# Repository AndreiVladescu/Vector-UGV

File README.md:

# V.E.C.T.O.R.

An 18-DOF hexapod research platform: a smart controller per leg on CAN, a Raspberry Pi CM5 carrier, camera and SDR payload, ELRS / Wi-Fi / 4G links. Built for the [PCBWay 9th Project Design Contest](https://www.pcbway.com/activity/9th-project-design-contest.html).

- `docs/`: spec, connector pinouts, power budget, servo names and calibration
- `hardware/`: one KiCad project per board, shared library in `lib/`
- `mechanical/`: Fusion 360 exports (STEP, STL), harness drawings
- `firmware/`: STM32C092 code for the leg and power nodes, CAN bootloader
- `software/`: CM5 / Pi 5 side: ROS 2 workspace, tools, Docker
- `protocol/vector.dbc`: CAN message definitions, used by firmware and host
- `test-tools/`: bench sketches, e.g. `servo_test` (Arduino Uno, set a servo angle over serial and read the pot)

Start with `docs/spec.md`.

## Try it without hardware

Everything below runs on a PC with Ubuntu 24.04 or Linux Mint 22 and ROS 2 Jazzy (install commands in [`software/README.md`](software/README.md#desktop-setup-mint-223--ubuntu-2404)). The leg nodes run their real firmware logic against simulated servos on a virtual CAN bus.

```sh
cd software/ros2_ws
source /opt/ros/jazzy/setup.zsh                 # or setup.bash
colcon build --symlink-install && source install/setup.zsh

# virtual CAN bus (again after every reboot)
sudo modprobe vcan
sudo ip link add dev vcan0 type vcan && sudo ip link set up vcan0

ros2 run vector_hw sim_legs vcan0 --calibrated --limits -45.8,45.8,-80.2,80.2,-149,17  # terminal 1: six legs
ros2 launch vector_bringup robot.launch.py hardware:=can can_interface:=vcan0   # terminal 2: robot + rviz
ros2 run teleop_twist_keyboard teleop_twist_keyboard                           # terminal 3: drive (i, j, l, J, L, t, b, k)
candump vcan0 | cantools decode ../../protocol/vector.dbc                      # optional: watch the bus
```

Each new terminal needs the two `source` lines. Stop `sim_legs` while the robot runs and the hardware drops out after 100 ms, the same as it would with a dead leg. Without `--calibrated` the legs start like fresh boards; `leg_config.py` calibrates them (see `software/README.md`).

Without CAN: `robot.launch.py` alone (mock joints), or `sim_gazebo.launch.py world:=rough level:=true` for physics.

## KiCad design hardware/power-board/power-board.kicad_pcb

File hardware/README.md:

# Hardware

One KiCad project per board: `side-board/`, `power-board/`, `carrier-cm5/`. The lib tables in each point to the shared library in `lib/`, so custom symbols and footprints go there.

- Connector pinouts come from `docs/interfaces.md`. Use the same footprint and pin order on both ends of a cable.
- Side board: draw the leg cell as one hierarchical sheet, use it three times, and copy the layout with KiCad's multichannel tools.
- Tag each fabbed revision (`side-board-revA`) and put the revision and git hash on the silkscreen. Gerbers, BOM and pick-and-place go in `<board>/production/<rev>/`.
- Hand assembly: 0402 minimum, one side where possible, test points and 0 Ω links on every rail.

`BOM_LCSC.csv` is a second way to buy the main parts for one robot: LCSC part numbers, quantities, prices and stock checked on 2026-10-08, and where each part is cheaper (LCSC, Mouser or TME). It loads straight into LCSC's BOM tool. Passives aren't in it yet.

## Power rails

Currents and loads are in `docs/power-budget.md`. No 5 V on the side boards: the CAN transceivers are 3.3 V parts (TI TCAN332DR).

```
PACK 4S3P 18650 (12.0–16.8 V)
│
└─ POWER BOARD ── BQ76952 high-side FETs ── VBAT
   │                                  (charging: BQ25798, fed by GX-12 12–24 V or USB-C PD 20 V)
   │
   ├─ LM5069 (hot-swap + e-stop) ── VBAT_L ──► SIDE BOARD L
   │                                  ├─ TPS56A37 ── 6V0_LEG1 ── 3× MG996R (+ pots)
   │                                  ├─ TPS56A37 ── 6V0_LEG2 ── 3× MG996R (+ pots)
   │                                  ├─ TPS56A37 ── 6V0_LEG3 ── 3× MG996R (+ pots)
   │                                  └─ low-Iq buck ── 3V3_LEG ── 3× STM32C092, 3× CAN xcvr,
   │                                                              3× VL53L1X, 3× INA181
   │
   ├─ LM5069 (hot-swap + e-stop) ── VBAT_R ──► SIDE BOARD R   (same as L)
   │
   ├─ 5 V / 6 A buck ── 5V_SYS ──► CARRIER
   │                                  ├─ CM5 ── 3V3 / 1V8 (CM5's own outputs)
   │                                  ├─ 2× USB-A (current-limit switches)
   │                                  ├─ SDR (AD9363), fan
   │                                  └─ 3V3_M2 ── Hailo M.2 (optional)
   │
   ├─ VBAT_SYS ──► CARRIER
   │                ├─ 3.8 V buck ── 3V8_LTE ── EC25-EUX
   │                └─ small 5 V buck ── gimbal (2× SG90)
   │
   └─ 3V3_PWR (TBD) ── STM32C092 on the power board, BQ76952 comms
```

3.3 V is made locally on each side board, not sent over the CAN harness: the STM32C0 ADC uses VDD as its reference, so a remote 3.3 V would put servo current noise on the pot and current readings, and a short on one side would take down the other.

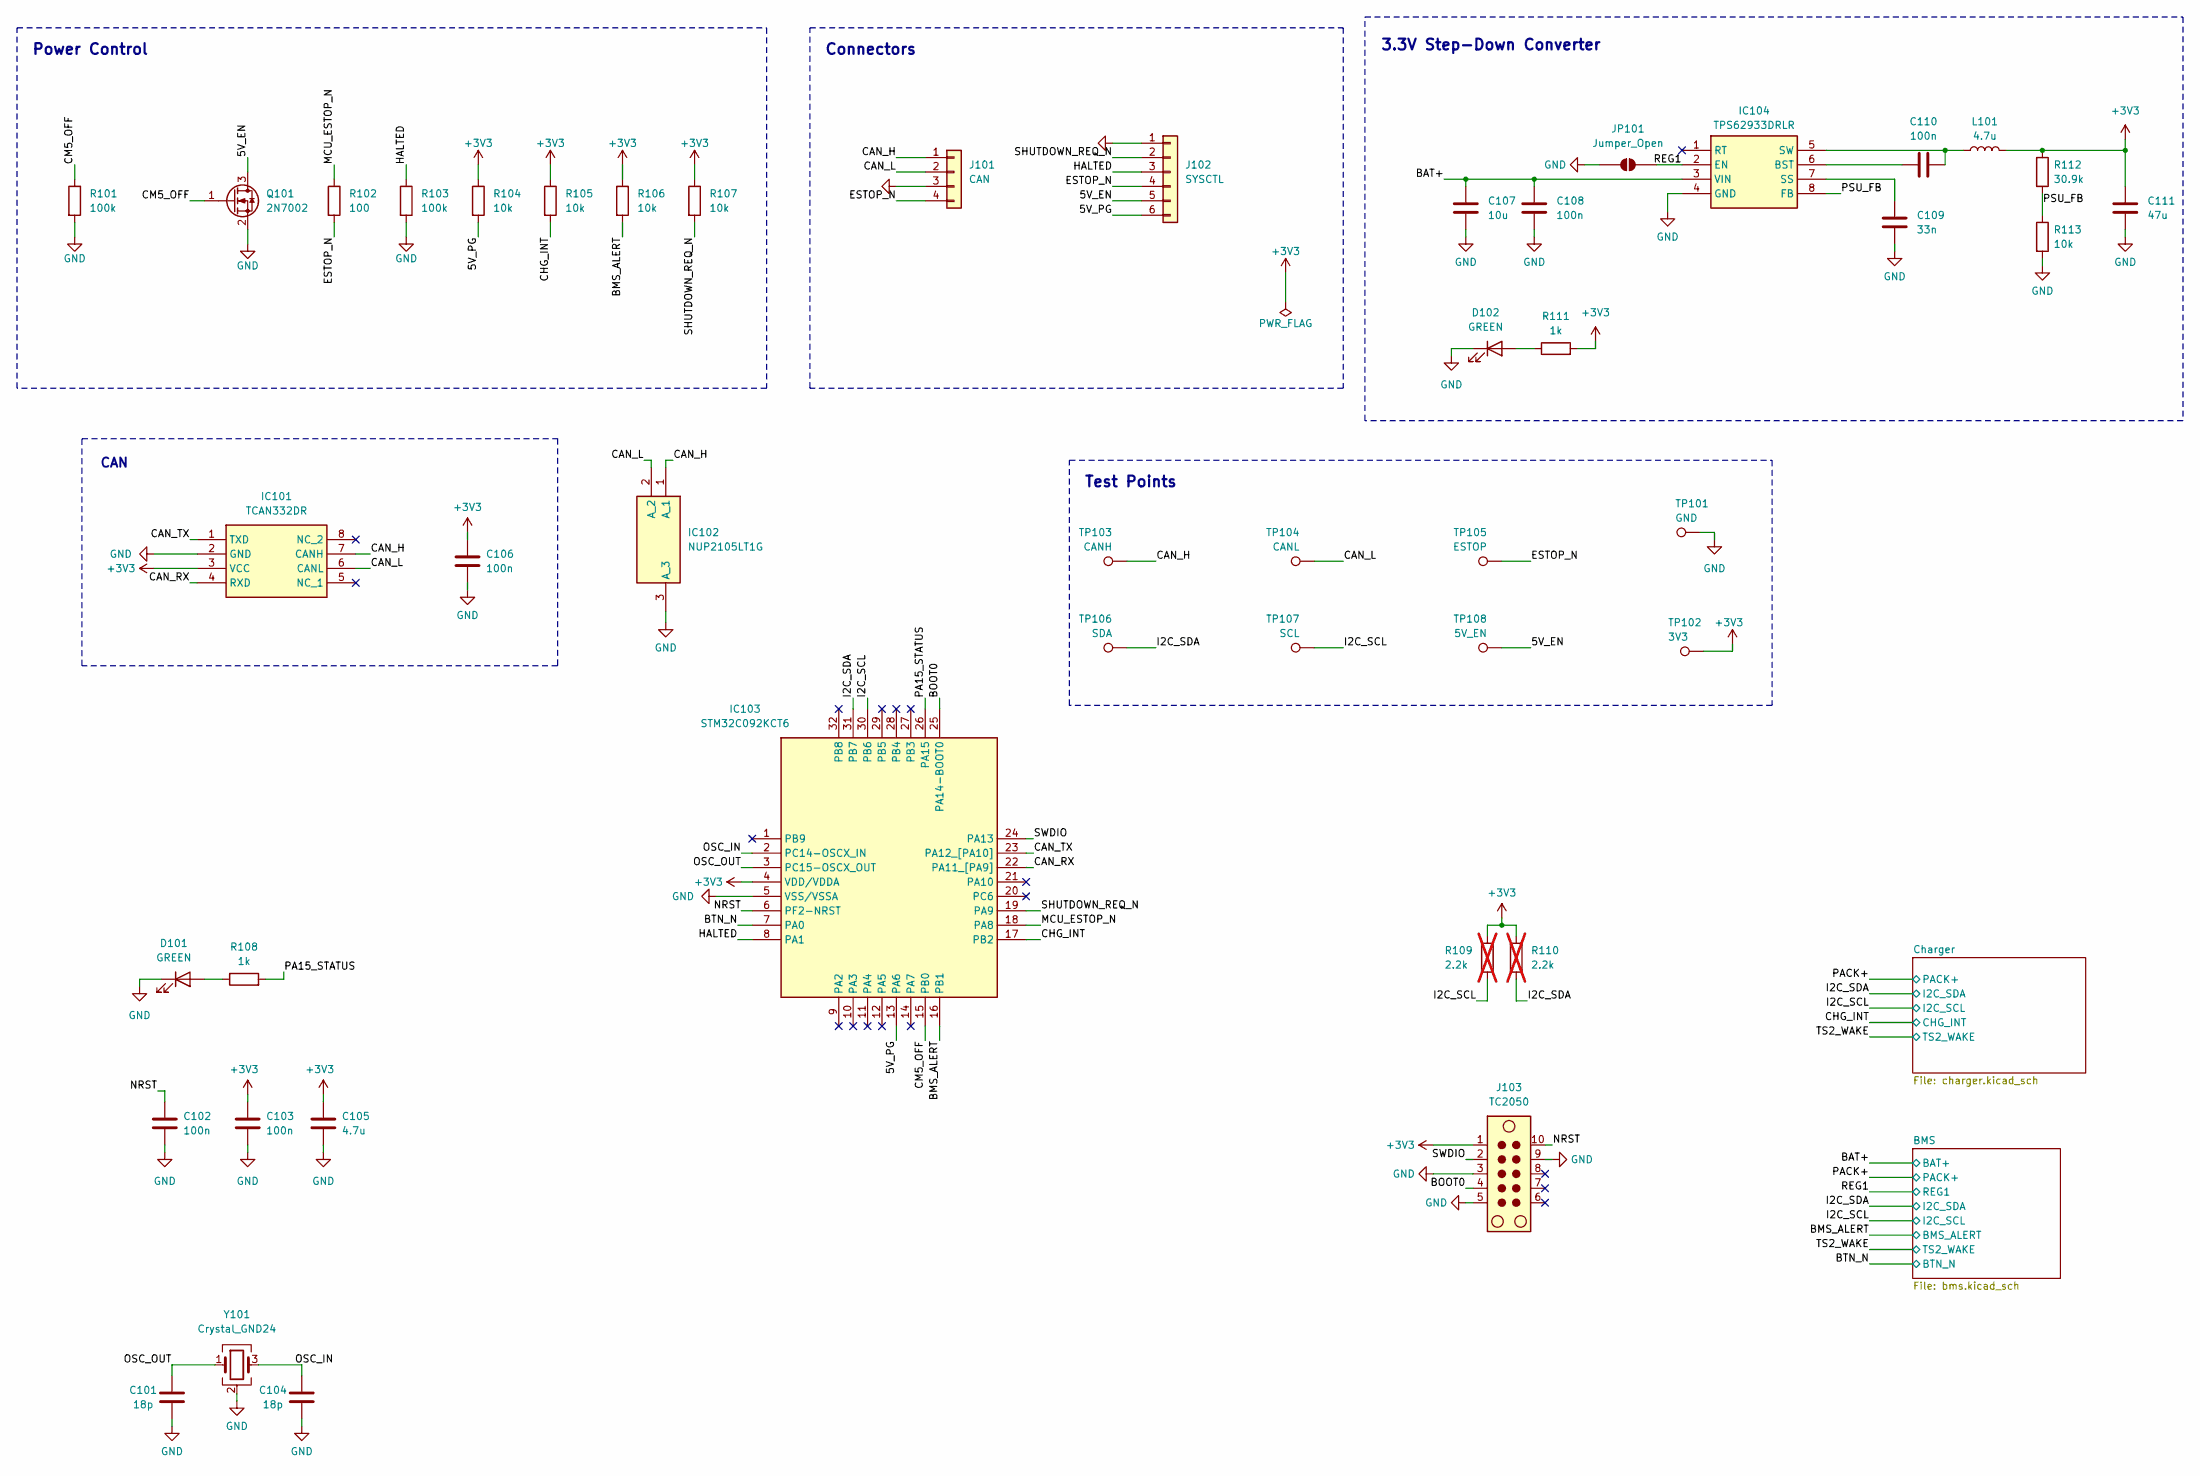
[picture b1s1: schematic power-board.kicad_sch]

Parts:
C101, C104: 18p; C_0805_2012Metric
C102, C103, C106, C108, C110: 100n; C_0805_2012Metric
C105: 4.7u; C_0805_2012Metric
C107: 10u; C_0805_2012Metric
C109: 33n; C_0805_2012Metric
C111: 47u; C_0805_2012Metric
D101, D102: GREEN; LED_0805_2012Metric
IC101: TCAN332DR; SOIC127P600X175-8N; Mouser Part Number 595-TCAN332DR
IC102: NUP2105LT1G; SOT96P237X111-3N; Mouser Part Number 863-NUP2105LT1G
IC103: STM32C092KCT6; QFP80P900X900X160-32N; Mouser Part Number 511-STM32C092KCT6
IC104: TPS62933DRLR; SOTFL50P160X60-8N; Mouser Part Number 595-TPS62933DRLR
J101: CAN; JST_XH_S4B-XH-A-1_1x04_P2.50mm_Horizontal
J102: SYSCTL; JST_XH_S6B-XH-A-1_1x06_P2.50mm_Horizontal
J103: TC2050; Tag-Connect_TC2050-IDC-FP_2x05_P1.27mm_Vertical
JP101: Jumper_Open; SolderJumper-2_P1.3mm_Open_Pad1.0x1.5mm
L101: 4.7u; INDPM4441X200N; Manufacturer_Part_Number SRP4020TA-4R7M
Q101: 2N7002; SOT-23
R101, R103: 100k; R_0603_1608Metric
R102: 100; R_0603_1608Metric
R104, R105, R106, R107: 10k; R_0603_1608Metric
R108, R111: 1k; R_0603_1608Metric
R109, R110: 2.2k; R_0603_1608Metric; not fitted
R112: 30.9k; R_0805_2012Metric
R113: 10k; R_0805_2012Metric
TP101: GND; TestPoint_Pad_D2.0mm
TP102: 3V3; TestPoint_Pad_D2.0mm
TP103: CANH; TestPoint_Pad_D2.0mm
TP104: CANL; TestPoint_Pad_D2.0mm
TP105: ESTOP; TestPoint_Pad_D2.0mm
TP106: SDA; TestPoint_Pad_D2.0mm
TP107: SCL; TestPoint_Pad_D2.0mm
TP108: 5V_EN; TestPoint_Pad_D2.0mm
Y101: Crystal_GND24; Crystal_SMD_2016-4Pin_2.0x1.6mm; Manufacturer_Part_Number K2B400001210

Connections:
+3V3: C103.2, C105.2, C106.2, C111.2, IC101.3 (VCC), IC103.4 (VDD/VDDA), J103.1, L101.2, R104.1, R105.1, R106.1, R107.1, R109.1, R110.2, R111.2, R112.1, TP102.1 (1_1)
/5V_EN: J102.5, Q101.3 (D), TP108.1 (1_1)
/5V_PG: IC103.13 (PA6), J102.6, R104.2
/BAT+: C107.2, C108.2, IC104.3 (VIN); also elsewhere on the board
/BMS_ALERT: IC103.16 (PB1), R106.2; also elsewhere on the board
/BOOT0: IC103.25 (PA14-BOOT0), J103.4
/BTN_N: IC103.7 (PA0); also elsewhere on the board
/CAN_H: IC101.7 (CANH), IC102.1 (A_1), J101.1, TP103.1 (1_1)
/CAN_L: IC101.6 (CANL), IC102.2 (A_2), J101.2, TP104.1 (1_1)
/CAN_RX: IC101.4 (RXD), IC103.22 (PA11_[PA9])
/CAN_TX: IC101.1 (TXD), IC103.23 (PA12_[PA10])
/CHG_INT: IC103.17 (PB2), R105.2; also elsewhere on the board
/CM5_OFF: IC103.15 (PB0), Q101.1 (G), R101.1
/ESTOP_N: J101.4, J102.4, R102.2, TP105.1 (1_1)
/HALTED: IC103.8 (PA1), J102.3, R103.1
/I2C_SCL: IC103.30 (PB6), R109.2, TP107.1 (1_1); also elsewhere on the board
/I2C_SDA: IC103.31 (PB7), R110.1, TP106.1 (1_1); also elsewhere on the board
/MCU_ESTOP_N: IC103.18 (PA8), R102.1
/NRST: C102.2, IC103.6 (PF2-NRST), J103.10
/OSC_IN: C104.2, IC103.2 (PC14-OSCX_IN), Y101.3
/OSC_OUT: C101.2, IC103.3 (PC15-OSCX_OUT), Y101.1
/PA15_STATUS: IC103.26 (PA15), R108.2
/PSU_FB: IC104.8 (FB), R112.2, R113.1
/REG1: IC104.2 (EN), JP101.2 (B); also elsewhere on the board
/SHUTDOWN_REQ_N: IC103.19 (PA9), J102.2, R107.2
/SWDIO: IC103.24 (PA13), J103.2
GND: C101.1, C102.1, C103.1, C104.1, C105.1, C106.1, C107.1, C108.1, C109.1, C111.1, D101.1 (K), D102.1 (K), IC101.2 (GND), IC102.3 (A_3), IC103.5 (VSS/VSSA), IC104.4 (GND), J101.3, J102.1, J103.3, J103.5, J103.9, JP101.1 (A), Q101.2 (S), R101.2, R103.2, R113.2, TP101.1 (1_1), Y101.2 (G), Y101.4 (G); also elsewhere on the board
unnamed: D101.2 (A), R108.1
unnamed: D102.2 (A), R111.1
unnamed: C110.1, IC104.6 (BST)
unnamed: C109.2, IC104.7 (SS)
unnamed: C110.2, IC104.5 (SW), L101.1

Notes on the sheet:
Test Points
Power Control
CAN
3.3V Step-Down Converter
Connectors

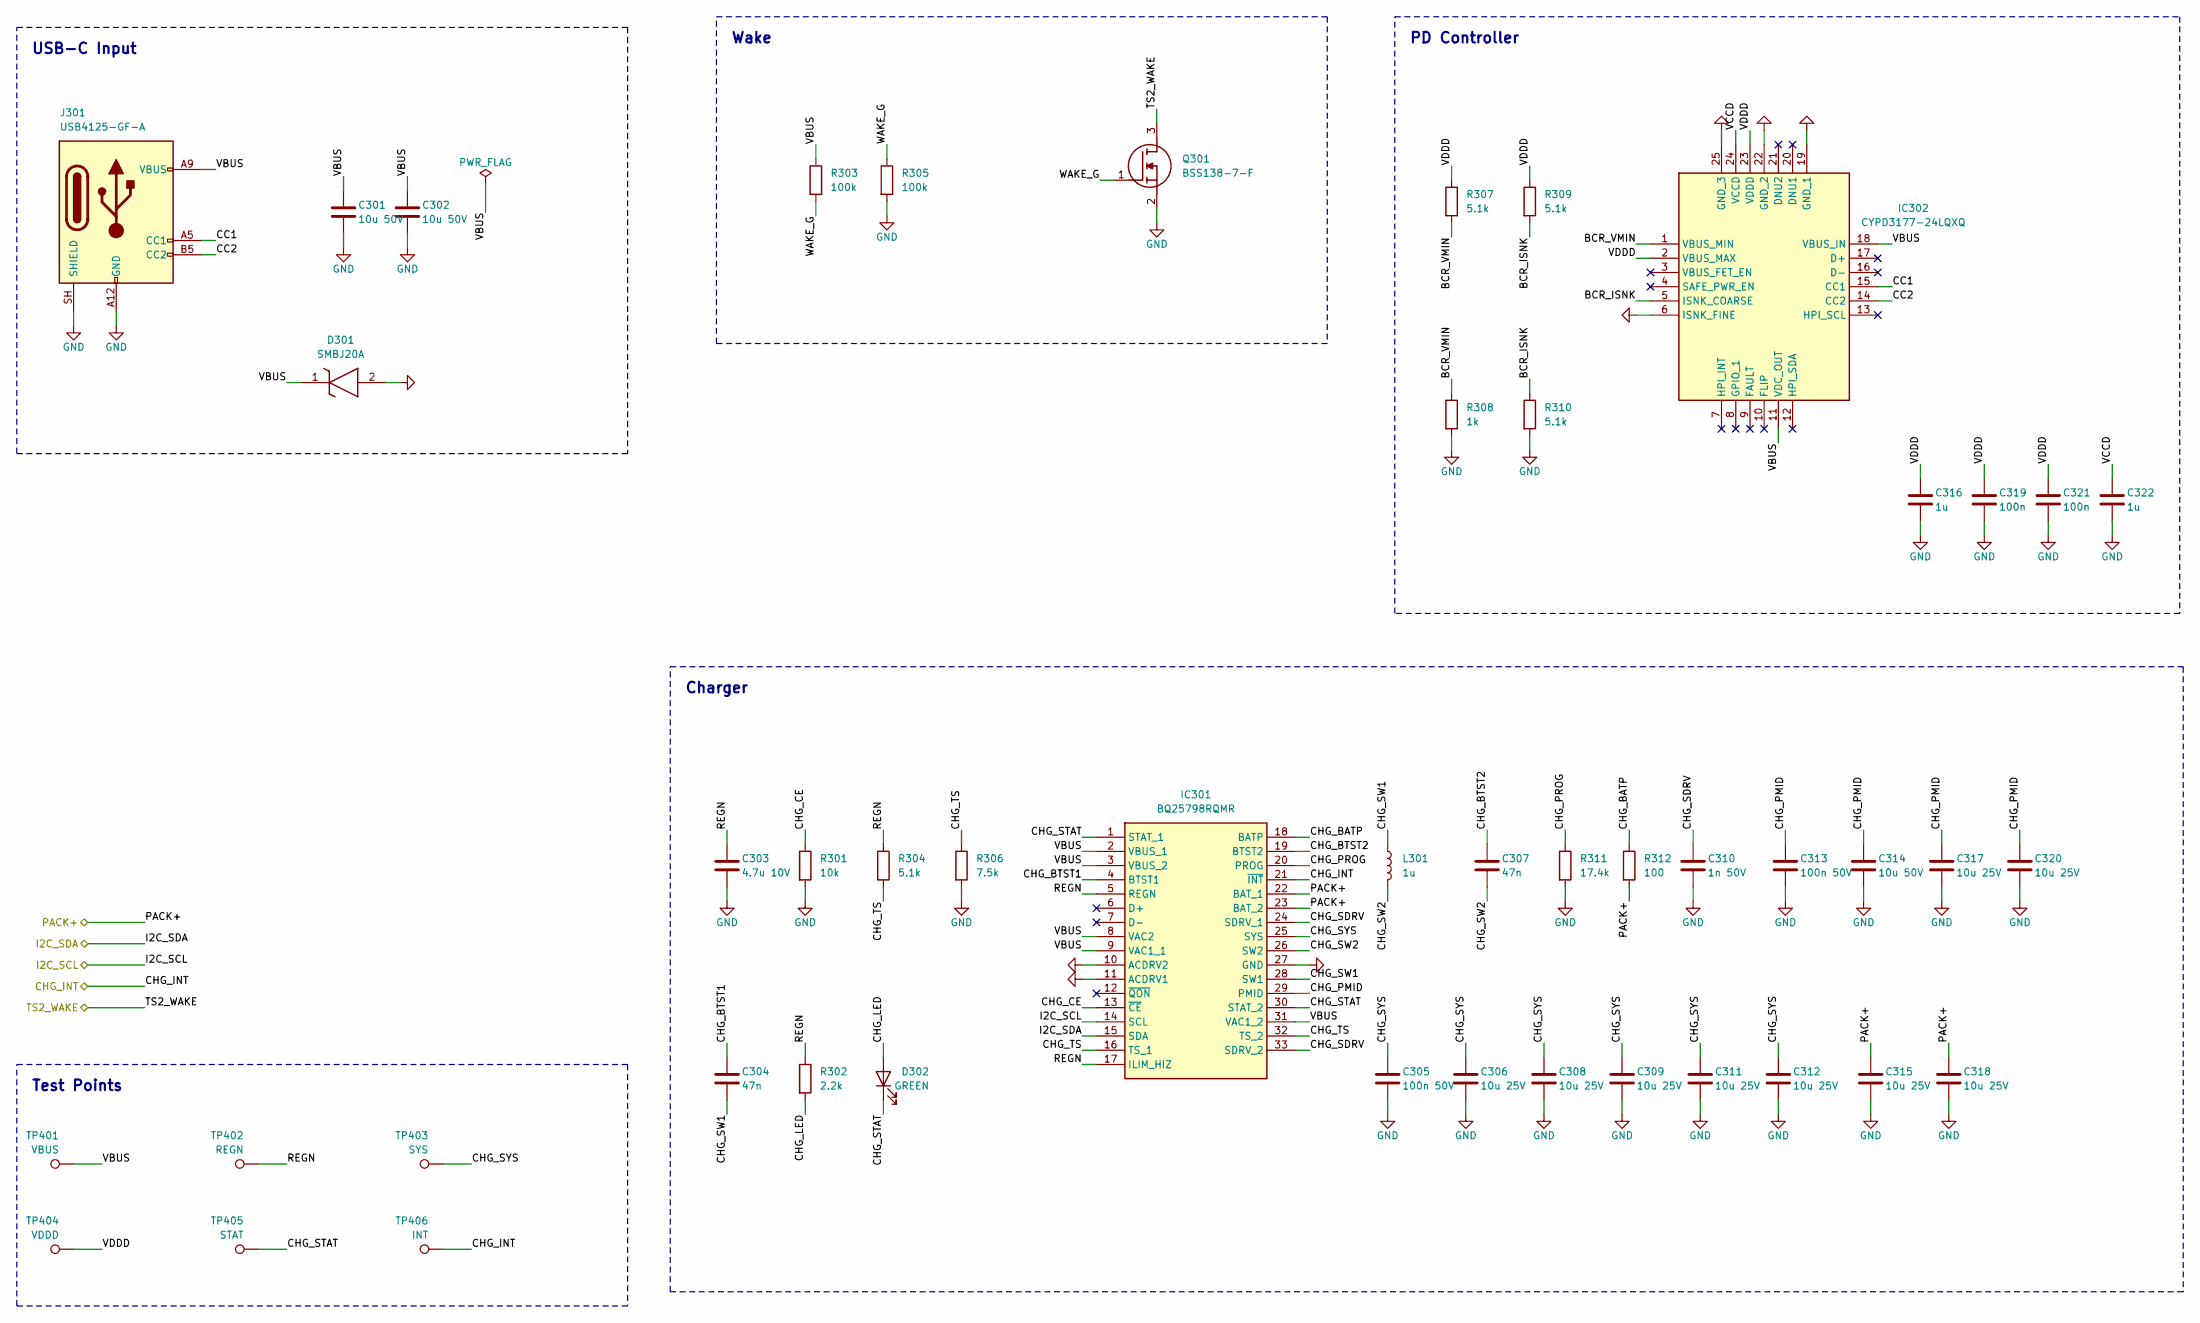
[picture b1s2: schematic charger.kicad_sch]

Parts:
C301, C302, C314: 10u 50V; C_1206_3216Metric
C303: 4.7u 10V; C_0805_2012Metric
C304, C307: 47n; C_0805_2012Metric
C305, C313: 100n 50V; C_0805_2012Metric
C306, C308, C309, C311, C312, C315, C317, C318, C320: 10u 25V; C_0805_2012Metric
C310: 1n 50V; C_0805_2012Metric
C316, C322: 1u; C_0805_2012Metric
C319, C321: 100n; C_0805_2012Metric
D301: SMBJ20A; DIOM5436X244N; Mouser Part Number 652-SMBJ20A
D302: GREEN; LED_0603_1608Metric
IC301: BQ25798RQMR; Mouser Part Number 595-BQ25798RQMR
IC302: CYPD3177-24LQXQ; QFN50P400X400X60-25N-D; Mouser Part Number 727-CYPD3177-24LQXQ
J301: USB4125-GF-A; USB_C_Receptacle_GCT_USB4125-xx-x_6P_TopMnt_Horizontal
L301: 1u; L_Coilcraft_XAL5030-XXX
Q301: BSS138-7-F; SOT96P240X115-3N; Mouser Part Number 621-BSS138-7-F
R301: 10k; R_0603_1608Metric
R302: 2.2k; R_0603_1608Metric
R303, R305: 100k; R_0603_1608Metric
R304, R307, R309, R310: 5.1k; R_0603_1608Metric
R306: 7.5k; R_0603_1608Metric
R308: 1k; R_0603_1608Metric
R311: 17.4k; R_0603_1608Metric
R312: 100; R_0603_1608Metric
TP401: VBUS; TestPoint_Pad_D2.0mm
TP402: REGN; TestPoint_Pad_D2.0mm
TP403: SYS; TestPoint_Pad_D2.0mm
TP404: VDDD; TestPoint_Pad_D2.0mm
TP405: STAT; TestPoint_Pad_D2.0mm
TP406: INT; TestPoint_Pad_D2.0mm

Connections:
/CHG_INT: IC301.21 (~INT), TP406.1 (1_1); also elsewhere on the board
/Charger/BCR_ISNK: IC302.5 (ISNK_COARSE), R309.2, R310.1
/Charger/BCR_VMIN: IC302.1 (VBUS_MIN), R307.2, R308.1
/Charger/CC1: IC302.15 (CC1), J301.A5 (CC1)
/Charger/CC2: IC302.14 (CC2), J301.B5 (CC2)
/Charger/CHG_BATP: IC301.18 (BATP), R312.1
/Charger/CHG_BTST1: C304.1, IC301.4 (BTST1)
/Charger/CHG_BTST2: C307.1, IC301.19 (BTST2)
/Charger/CHG_CE: IC301.13 (~CE), R301.1
/Charger/CHG_LED: D302.2 (A), R302.2
/Charger/CHG_PMID: C313.1, C314.1, C317.1, C320.1, IC301.29 (PMID)
/Charger/CHG_PROG: IC301.20 (PROG), R311.1
/Charger/CHG_SDRV: C310.1, IC301.24 (SDRV_1), IC301.33 (SDRV_2)
/Charger/CHG_STAT: D302.1 (K), IC301.1 (STAT_1), IC301.30 (STAT_2), TP405.1 (1_1)
/Charger/CHG_SW1: C304.2, IC301.28 (SW1), L301.1
/Charger/CHG_SW2: C307.2, IC301.26 (SW2), L301.2
/Charger/CHG_SYS: C305.1, C306.1, C308.1, C309.1, C311.1, C312.1, IC301.25 (SYS), TP403.1 (1_1)
/Charger/CHG_TS: IC301.16 (TS_1), IC301.32 (TS_2), R304.2, R306.1
/Charger/REGN: C303.1, IC301.5 (REGN), IC301.17 (ILIM_HIZ), R302.1, R304.1, TP402.1 (1_1)
/Charger/VBUS: C301.1, C302.1, D301.1 (K), IC301.2 (VBUS_1), IC301.3 (VBUS_2), IC301.8 (VAC2), IC301.9 (VAC1_1), IC301.31 (VAC1_2), IC302.11 (VDC_OUT), IC302.18 (VBUS_IN), J301.A9 (VBUS), J301.B9 (VBUS), R303.1, TP401.1 (1_1)
/Charger/VCCD: C322.1, IC302.24 (VCCD)
/Charger/VDDD: C316.1, C319.1, C321.1, IC302.2 (VBUS_MAX), IC302.23 (VDDD), R307.1, R309.1, TP404.1 (1_1)
/Charger/WAKE_G: Q301.1 (G), R303.2, R305.1
/I2C_SCL: IC301.14 (SCL); also elsewhere on the board
/I2C_SDA: IC301.15 (SDA); also elsewhere on the board
/PACK+: C315.1, C318.1, IC301.22 (BAT_1), IC301.23 (BAT_2), R312.2; also elsewhere on the board
/TS2_WAKE: Q301.3 (D); also elsewhere on the board
GND: C301.2, C302.2, C303.2, C305.2, C306.2, C308.2, C309.2, C310.2, C311.2, C312.2, C313.2, C314.2, C315.2, C316.2, C317.2, C318.2, C319.2, C320.2, C321.2, C322.2, D301.2 (A), IC301.10 (ACDRV2), IC301.11 (ACDRV1), IC301.27 (GND), IC302.6 (ISNK_FINE), IC302.19 (GND_1), IC302.22 (GND_2), IC302.25 (GND_3), J301.A12 (GND), J301.B12 (GND), J301.SH (SHIELD), Q301.2 (S), R301.2, R305.2, R306.2, R308.2, R310.2, R311.2; also elsewhere on the board

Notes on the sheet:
Wake
Test Points
PD Controller
Charger
USB-C Input

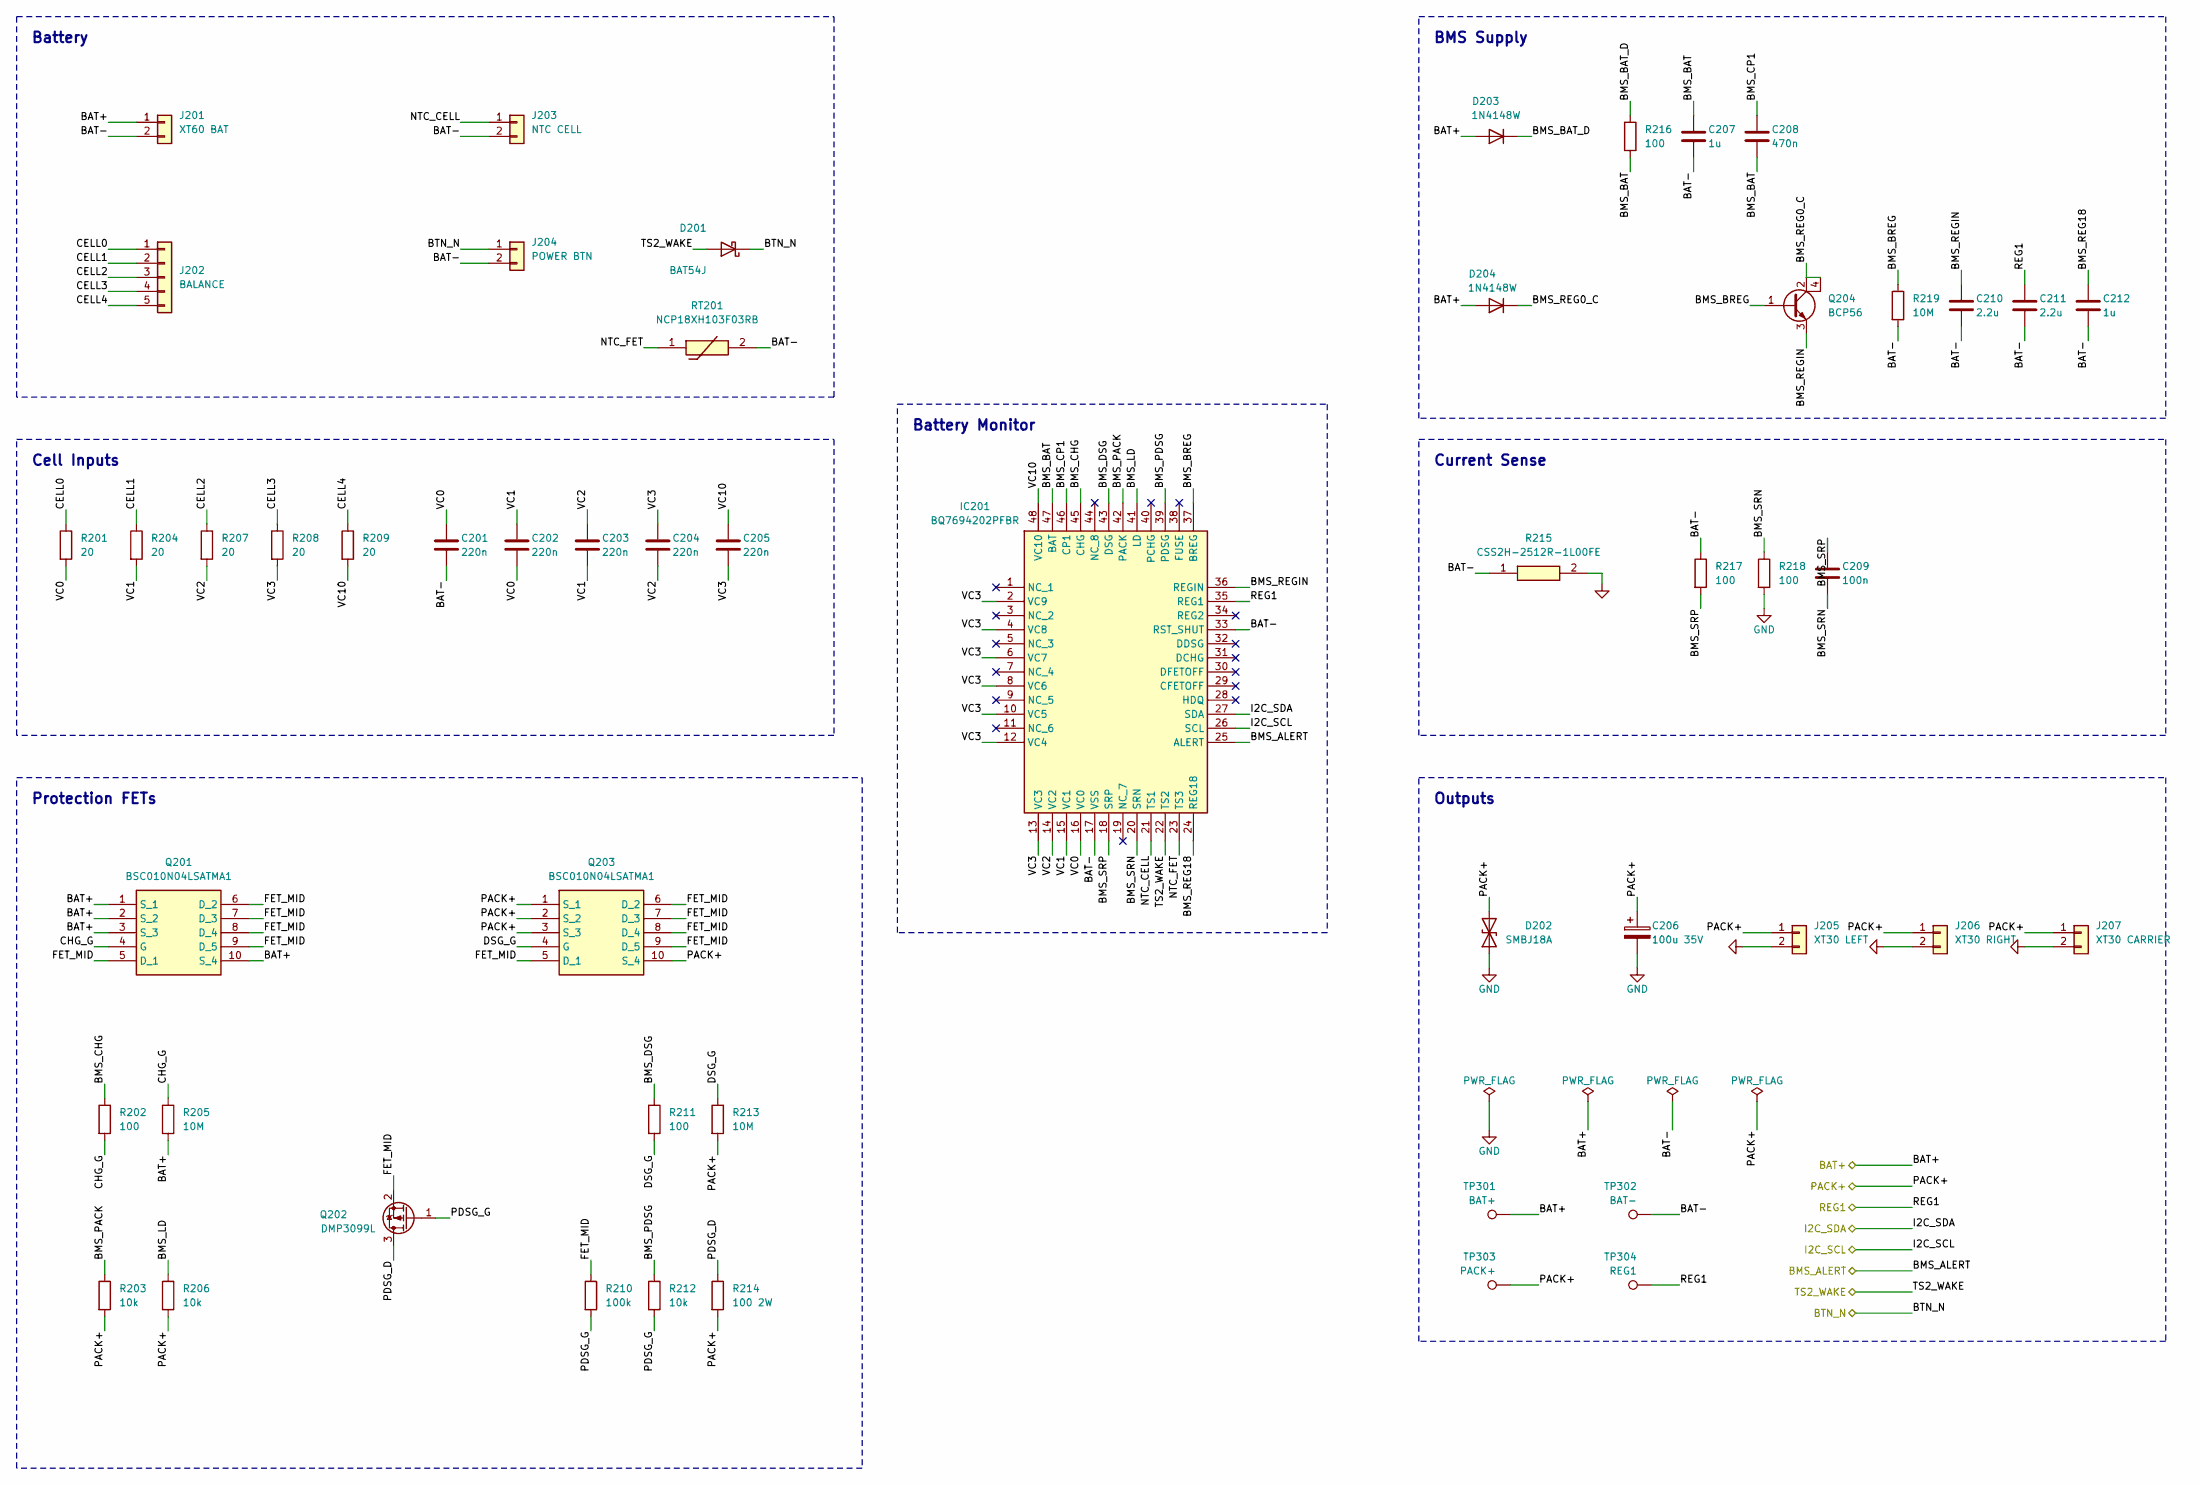
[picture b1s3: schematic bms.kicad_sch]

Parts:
C201, C202, C203, C204, C205: 220n; C_0805_2012Metric
C206: 100u 35V; CP_Elec_8x10.5
C207, C212: 1u; C_0805_2012Metric
C208: 470n; C_0805_2012Metric
C209: 100n; C_0805_2012Metric
C210, C211: 2.2u; C_0805_2012Metric
D201: BAT54J; D_SOD-323F
D202: SMBJ18A; D_SMB
D203, D204: 1N4148W; D_SOD-123
IC201: BQ7694202PFBR; QFP50P900X900X120-48N; Mouser Part Number 595-BQ7694202PFBR
J201: XT60 BAT; AMASS_XT60PW-M_1x02_P7.20mm_Horizontal
J202: BALANCE; JST_XH_B5B-XH-A_1x05_P2.50mm_Vertical
J203: NTC CELL; JST_PH_B2B-PH-K_1x02_P2.00mm_Vertical
J204: POWER BTN; JST_PH_B2B-PH-K_1x02_P2.00mm_Vertical
J205: XT30 LEFT; AMASS_XT30PW-M_1x02_P2.50mm_Horizontal
J206: XT30 RIGHT; AMASS_XT30PW-M_1x02_P2.50mm_Horizontal
J207: XT30 CARRIER; AMASS_XT30PW-M_1x02_P2.50mm_Horizontal
Q201, Q203: BSC010N04LSATMA1; Mouser Part Number 726-BSC010N04LSATMA1
Q202: DMP3099L; SOT-23
Q204: BCP56; SOT-223
R201, R204, R207, R208, R209: 20; R_0603_1608Metric
R202, R211, R216, R217, R218: 100; R_0603_1608Metric
R203, R206, R212: 10k; R_0603_1608Metric
R205, R213, R219: 10M; R_0603_1608Metric
R210: 100k; R_0603_1608Metric
R214: 100 2W; R_2512_6332Metric
R215: CSS2H-2512R-1L00FE; CSS2H2512R1L00FE; Mouser Part Number 652-CSS2H2512R1L00FE
RT201: NCP18XH103F03RB; THRMC1608X95N; Mouser Part Number 81-NCP18XH103F03RB
TP301: BAT+; TestPoint_Pad_D2.0mm
TP302: BAT-; TestPoint_Pad_D2.0mm
TP303: PACK+; TestPoint_Pad_D2.0mm
TP304: REG1; TestPoint_Pad_D2.0mm

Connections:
/BAT+: D203.2 (A), D204.2 (A), J201.1, Q201.1 (S_1), Q201.2 (S_2), Q201.3 (S_3), Q201.10 (S_4), R205.2, TP301.1 (1_1); also elsewhere on the board
/BMS/BAT-: C201.2, C207.2, C210.2, C211.2, C212.2, IC201.17 (VSS), IC201.33 (RST_SHUT), J201.2, J203.2, J204.2, R215.1, R217.1, R219.2, RT201.2, TP302.1 (1_1)
/BMS/BMS_BAT: C207.1, C208.2, IC201.47 (BAT), R216.2
/BMS/BMS_BAT_D: D203.1 (K), R216.1
/BMS/BMS_BREG: IC201.37 (BREG), Q204.1 (B), R219.1
/BMS/BMS_CHG: IC201.45 (CHG), R202.1
/BMS/BMS_CP1: C208.1, IC201.46 (CP1)
/BMS/BMS_DSG: IC201.43 (DSG), R211.1
/BMS/BMS_LD: IC201.41 (LD), R206.1
/BMS/BMS_PACK: IC201.42 (PACK), R203.1
/BMS/BMS_PDSG: IC201.39 (PDSG), R212.1
/BMS/BMS_REG0_C: D204.1 (K), Q204.2 (C), Q204.4 (C)
/BMS/BMS_REG18: C212.1, IC201.24 (REG18)
/BMS/BMS_REGIN: C210.1, IC201.36 (REGIN), Q204.3 (E)
/BMS/BMS_SRN: C209.2, IC201.20 (SRN), R218.1
/BMS/BMS_SRP: C209.1, IC201.18 (SRP), R217.2
/BMS/CELL0: J202.1, R201.1
/BMS/CELL1: J202.2, R204.1
/BMS/CELL2: J202.3, R207.1
/BMS/CELL3: J202.4, R208.1
/BMS/CELL4: J202.5, R209.1
/BMS/CHG_G: Q201.4 (G), R202.2, R205.1
/BMS/DSG_G: Q203.4 (G), R211.2, R213.1
/BMS/FET_MID: Q201.5 (D_1), Q201.6 (D_2), Q201.7 (D_3), Q201.8 (D_4), Q201.9 (D_5), Q202.2 (S), Q203.5 (D_1), Q203.6 (D_2), Q203.7 (D_3), Q203.8 (D_4), Q203.9 (D_5), R210.1
/BMS/NTC_CELL: IC201.21 (TS1), J203.1
/BMS/NTC_FET: IC201.23 (TS3), RT201.1
/BMS/PDSG_D: Q202.3 (D), R214.1
/BMS/PDSG_G: Q202.1 (G), R210.2, R212.2
/BMS/VC0: C201.1, C202.2, IC201.16 (VC0), R201.2
/BMS/VC1: C202.1, C203.2, IC201.15 (VC1), R204.2
/BMS/VC2: C203.1, C204.2, IC201.14 (VC2), R207.2
/BMS/VC3: C204.1, C205.2, IC201.2 (VC9), IC201.4 (VC8), IC201.6 (VC7), IC201.8 (VC6), IC201.10 (VC5), IC201.12 (VC4), IC201.13 (VC3), R208.2
/BMS/VC10: C205.1, IC201.48 (VC10), R209.2
/BMS_ALERT: IC201.25 (ALERT); also elsewhere on the board
/BTN_N: D201.1 (K), J204.1; also elsewhere on the board
/I2C_SCL: IC201.26 (SCL); also elsewhere on the board
/I2C_SDA: IC201.27 (SDA); also elsewhere on the board
/PACK+: C206.1, D202.2 (A2), J205.1, J206.1, J207.1, Q203.1 (S_1), Q203.2 (S_2), Q203.3 (S_3), Q203.10 (S_4), R203.2, R206.2, R213.2, R214.2, TP303.1 (1_1); also elsewhere on the board
/REG1: C211.1, IC201.35 (REG1), TP304.1 (1_1); also elsewhere on the board
/TS2_WAKE: D201.2 (A), IC201.22 (TS2); also elsewhere on the board
GND: C206.2, D202.1 (A1), J205.2, J206.2, J207.2, R215.2, R218.2; also elsewhere on the board

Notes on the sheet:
BMS Supply
Outputs
Battery Monitor
Current Sense
Cell Inputs
Battery
Protection FETs

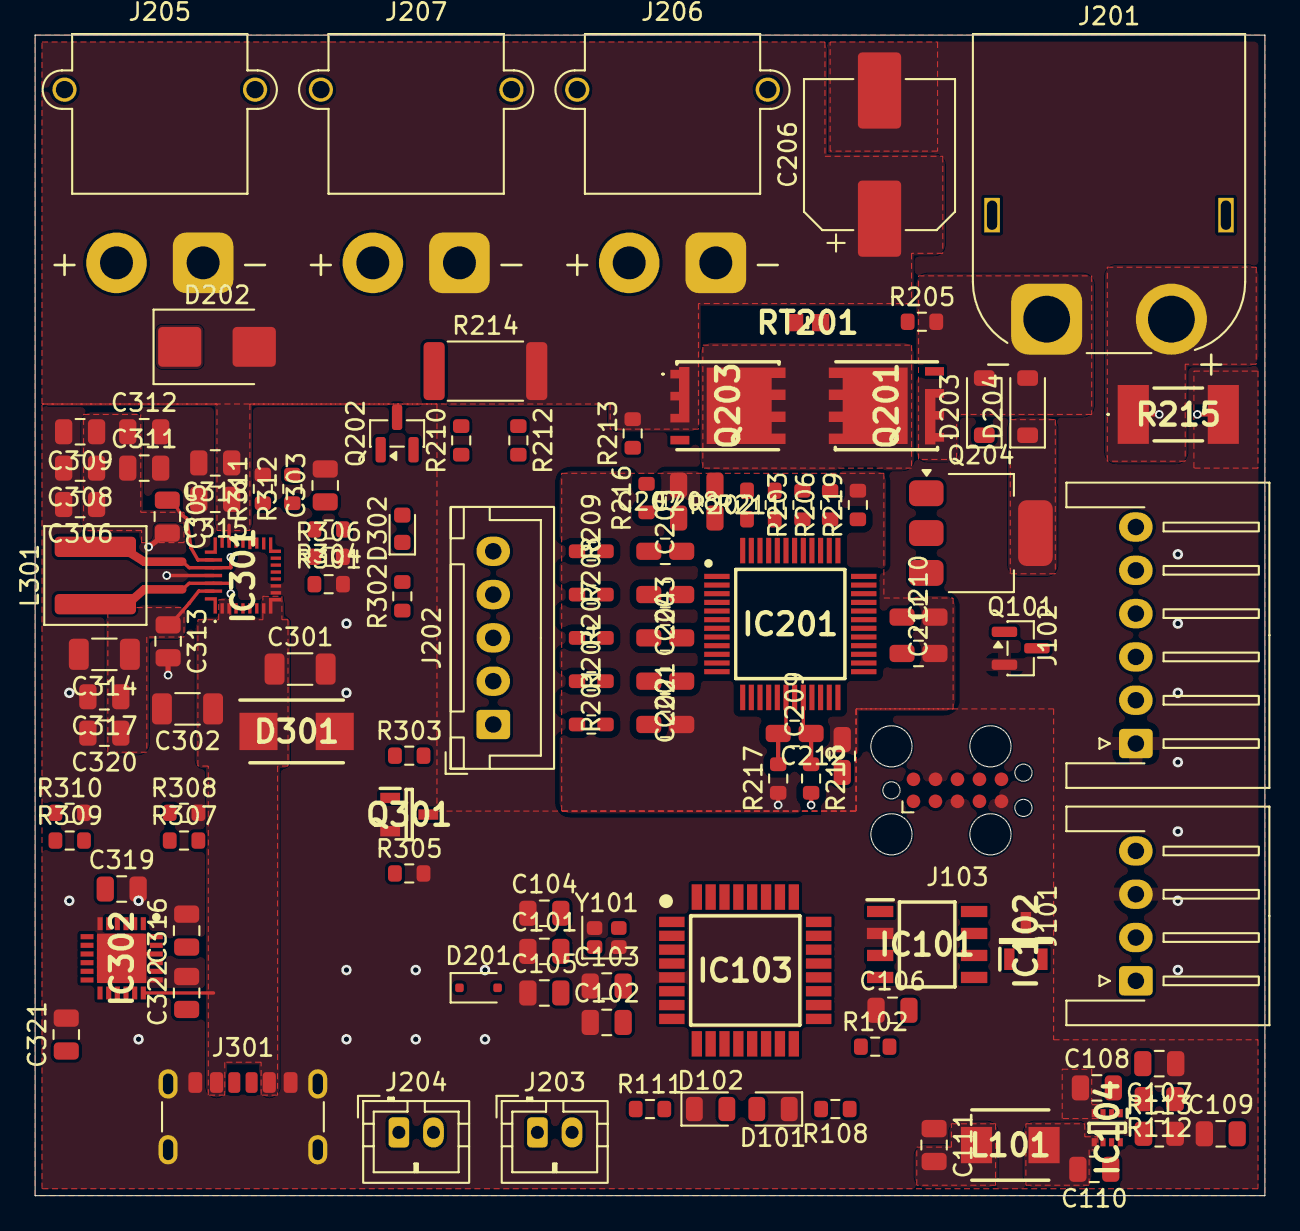
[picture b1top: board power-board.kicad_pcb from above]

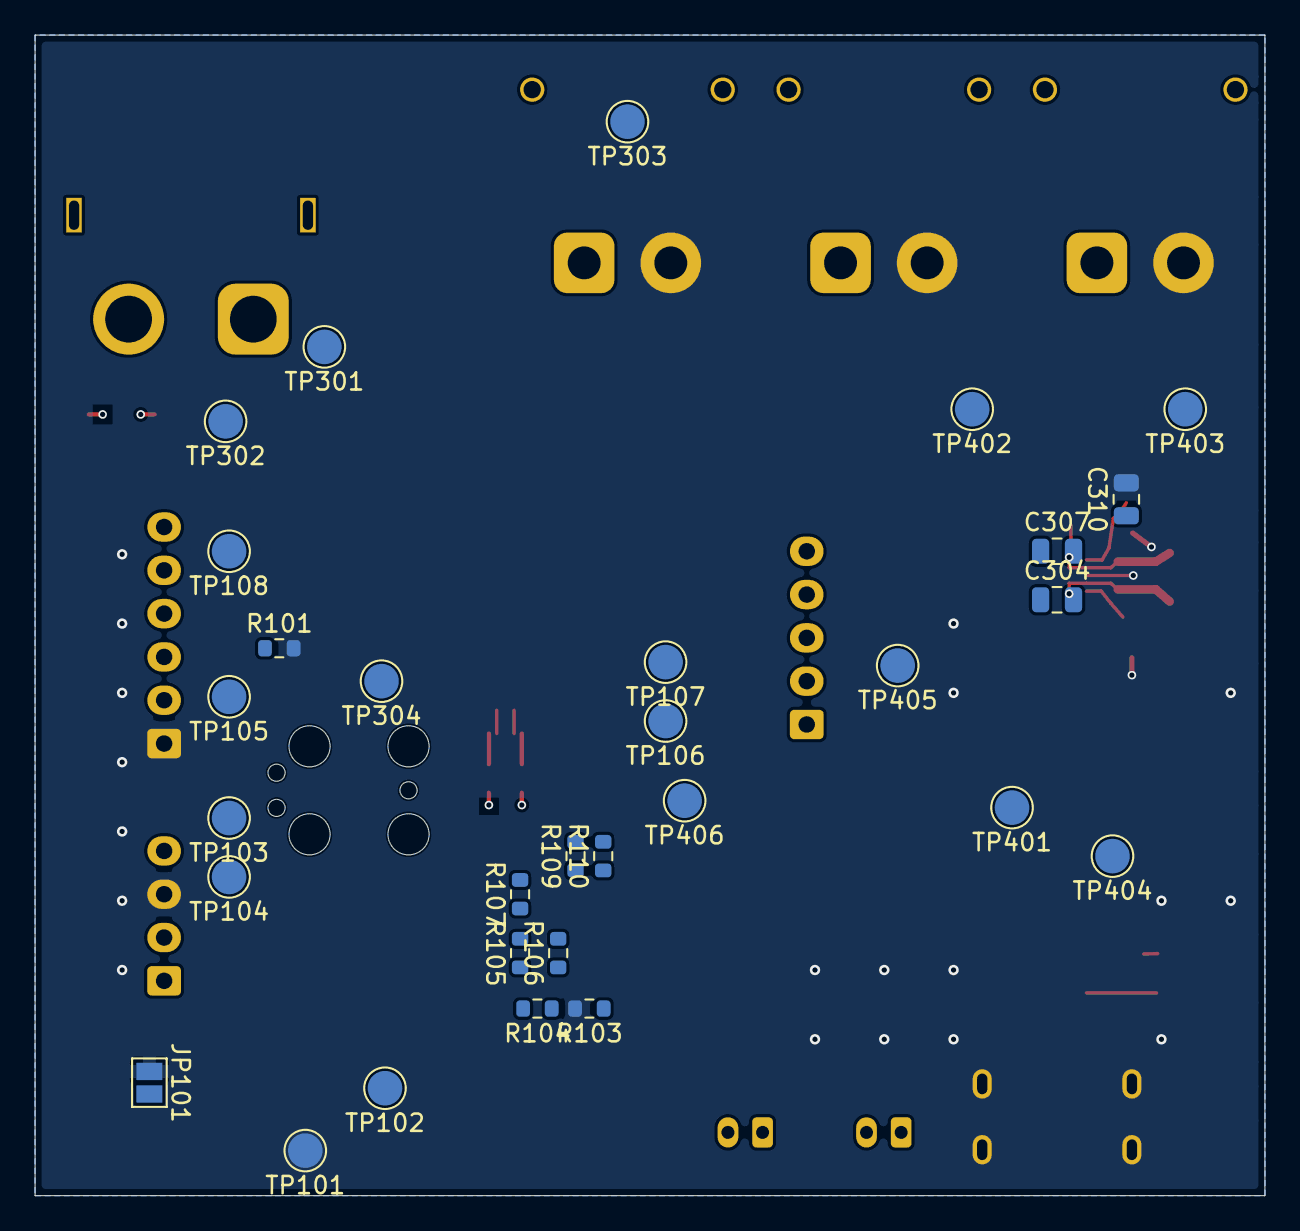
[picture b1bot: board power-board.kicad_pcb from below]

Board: 4 copper layers, 71.0 x 67.0 mm, 144 parts (30 on the bottom side), 88 nets.
